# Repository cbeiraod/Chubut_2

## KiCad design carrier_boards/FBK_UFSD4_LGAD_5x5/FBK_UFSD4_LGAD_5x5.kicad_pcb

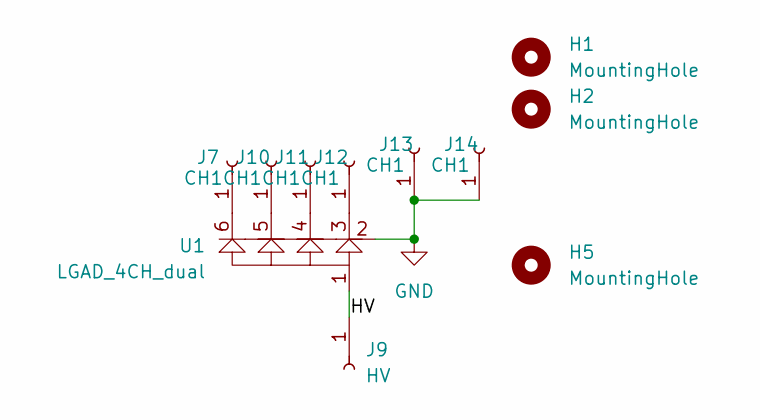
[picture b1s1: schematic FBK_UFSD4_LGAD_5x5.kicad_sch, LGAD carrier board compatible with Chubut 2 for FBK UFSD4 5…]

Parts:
H1, H2, H5: MountingHole; MILL-MAX_7625-0-00-15-00-00-03-0_alignment_hole
J7, J10, J11, J12, J13, J14: CH1; MILL-MAX_0965-0-15-20-80-14-11-0_contact
J9: HV; MILL-MAX_0965-0-15-20-80-14-11-0_contact
U1: LGAD_4CH_dual; FBK-UFSD4_5x5_Diagonal

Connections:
/HV: J9.1, U1.1
GND: J13.1, J14.1, U1.2
unnamed: J7.1, U1.6
unnamed: J10.1, U1.5
unnamed: J11.1, U1.4
unnamed: J12.1, U1.3

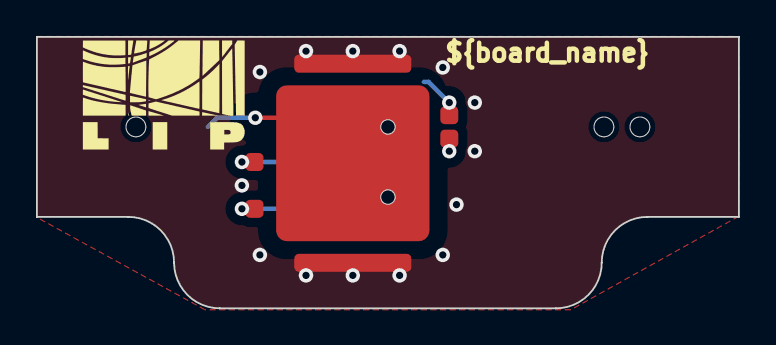
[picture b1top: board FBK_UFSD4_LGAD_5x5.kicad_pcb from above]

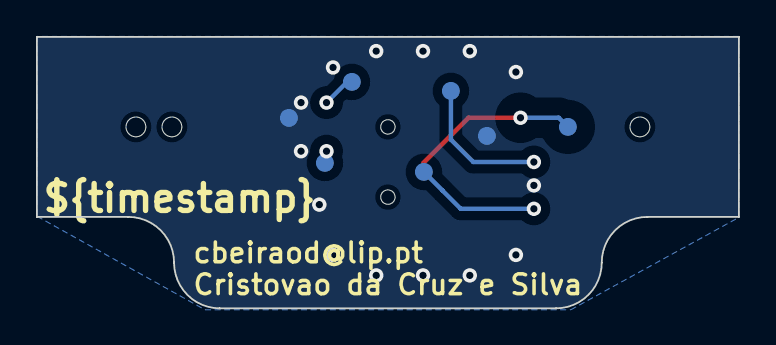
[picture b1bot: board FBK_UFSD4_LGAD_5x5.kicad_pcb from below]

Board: 2 copper layers, 39.0 x 15.1 mm, 11 parts (7 on the bottom side), 6 nets.

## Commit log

2023-07-20 Added a fottprint for the 5x5 FBK UFSD4 LGAD assuming wire bonds to the diagonal pixels
2023-07-20 Added carrier for the FBK UFSD 5x5 LGAD
